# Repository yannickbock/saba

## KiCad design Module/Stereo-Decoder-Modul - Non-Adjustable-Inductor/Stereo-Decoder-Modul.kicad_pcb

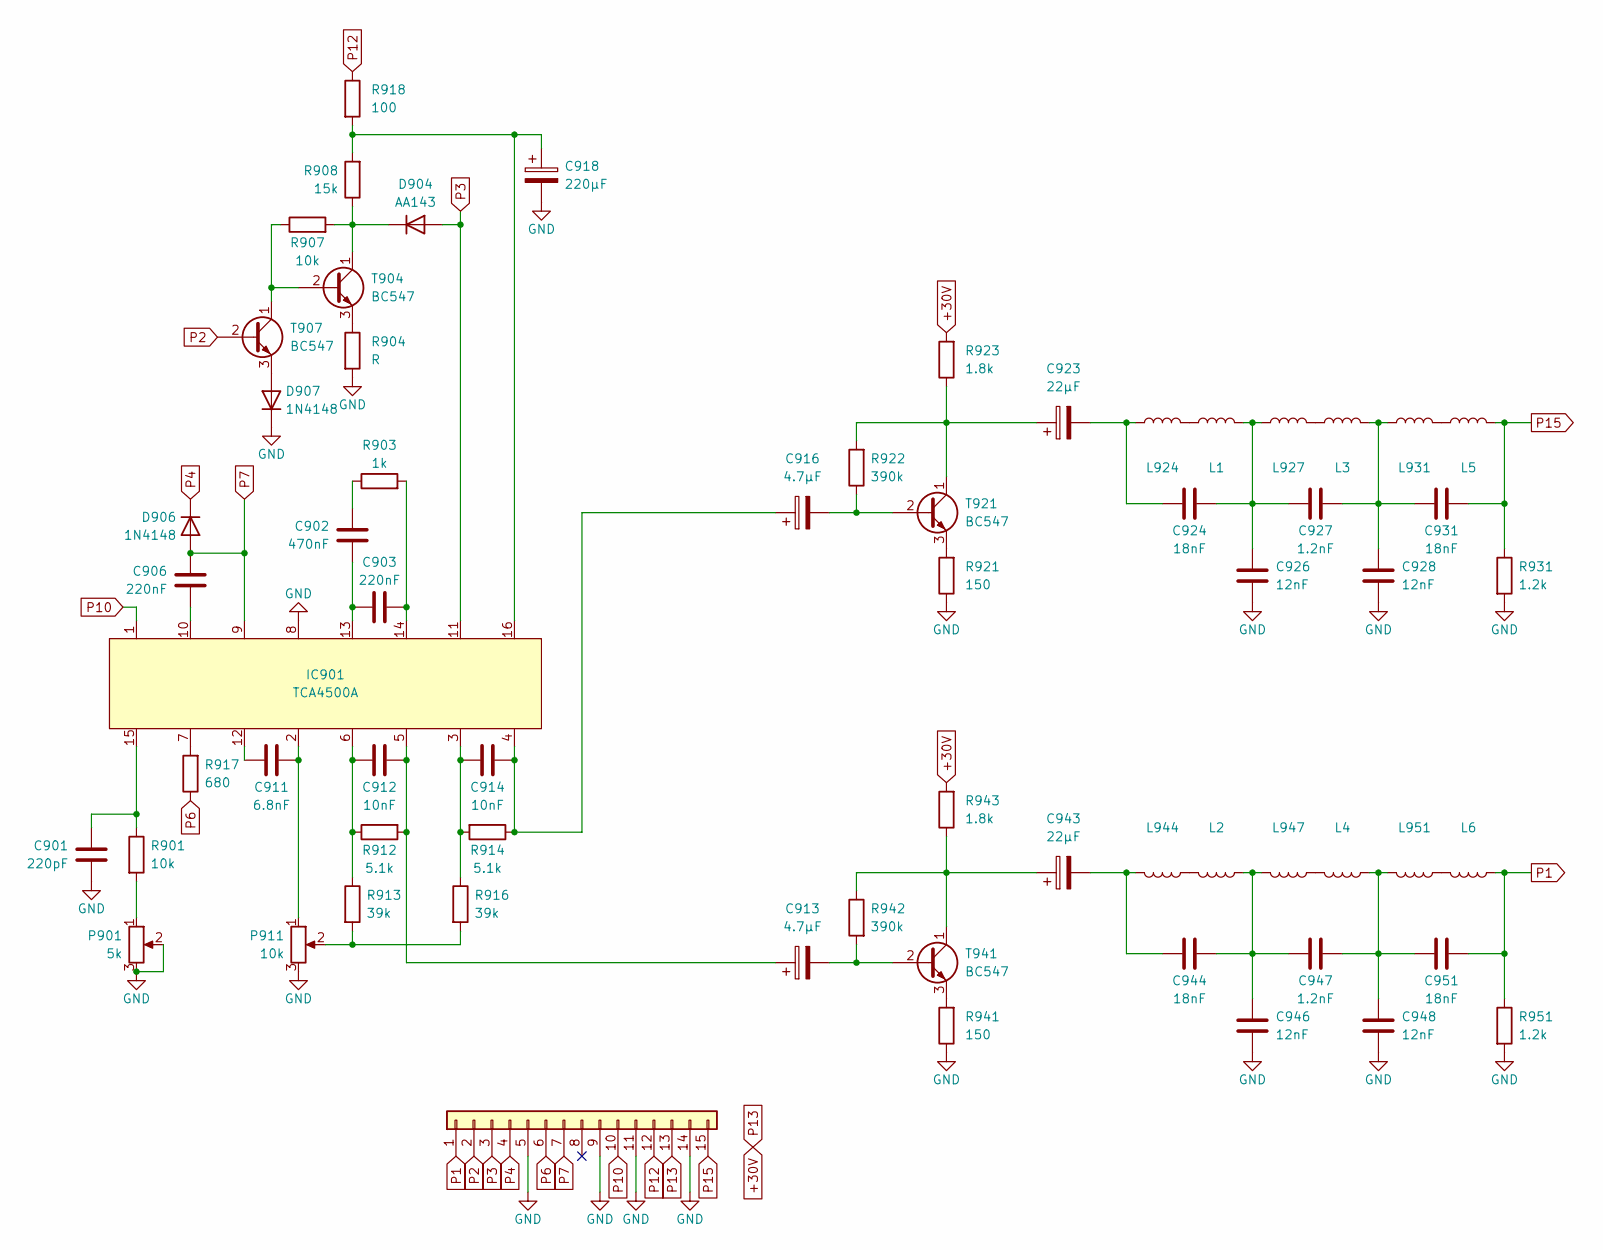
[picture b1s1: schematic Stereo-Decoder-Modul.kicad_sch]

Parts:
C901: 220pF; C_Rect_L7.2mm_W3.0mm_P5.00mm_FKS2_FKP2_MKS2_MKP2
C902: 470nF; C_Rect_L7.2mm_W3.0mm_P5.00mm_FKS2_FKP2_MKS2_MKP2
C903, C906: 220nF; C_Rect_L7.2mm_W3.0mm_P5.00mm_FKS2_FKP2_MKS2_MKP2
C911: 6.8nF; C_Rect_L7.2mm_W3.0mm_P5.00mm_FKS2_FKP2_MKS2_MKP2
C912, C914: 10nF; C_Rect_L10.0mm_W3.0mm_P7.50mm_MKS4
C913, C916: 4.7µF; C_Rect_L7.2mm_W7.2mm_P5.00mm_FKS2_FKP2_MKS2_MKP2
C918: 220µF; CP_Radial_D8.0mm_P3.50mm
C923, C943: 22µF; CP_Radial_D5.0mm_P2.00mm
C924, C931, C944, C951: 18nF; C_Rect_L10.0mm_W3.0mm_P7.50mm_MKS4
C926, C928, C946, C948: 12nF; C_Rect_L10.0mm_W3.0mm_P7.50mm_MKS4
C927, C947: 1.2nF; C_Rect_L10.0mm_W3.0mm_P7.50mm_MKS4
D904: AA143; D_DO-35_SOD27_P5.08mm_Vertical_AnodeUp
D906, D907: 1N4148; D_DO-35_SOD27_P5.08mm_Vertical_AnodeUp
IC901: TCA4500A; DIP-16_W7.62mm_LongPads
J1: Conn_01x15; Connector_01x15_5mm
L1, L2, L3, L4, L5, L6, L924, L927, L931, L944, L947, L951: 3.3mH-4.7mH; L_Axial_L11.0mm_D4.5mm_P5.08mm_Vertical_Fastron_MECC
P901: 5k; Potentiometer_Piher_PT-10-H01_Horizontal
P911: 10k; Potentiometer_Piher_PT-10-H01_Horizontal
R901, R907: 10k; R_Axial_DIN0207_L6.3mm_D2.5mm_P5.08mm_Vertical
R903: 1k; R_Axial_DIN0207_L6.3mm_D2.5mm_P5.08mm_Vertical
R904: R; R_Axial_DIN0207_L6.3mm_D2.5mm_P5.08mm_Vertical
R908: 15k; R_Axial_DIN0207_L6.3mm_D2.5mm_P5.08mm_Vertical
R912, R914: 5.1k; R_Axial_DIN0207_L6.3mm_D2.5mm_P2.54mm_Vertical
R913, R916: 39k; R_Axial_DIN0207_L6.3mm_D2.5mm_P5.08mm_Vertical
R917: 680; R_Axial_DIN0207_L6.3mm_D2.5mm_P5.08mm_Vertical
R918: 100; R_Axial_DIN0207_L6.3mm_D2.5mm_P5.08mm_Vertical
R921, R941: 150; R_Axial_DIN0207_L6.3mm_D2.5mm_P5.08mm_Vertical
R922, R942: 390k; R_Axial_DIN0207_L6.3mm_D2.5mm_P5.08mm_Vertical
R923, R943: 1.8k; R_Axial_DIN0207_L6.3mm_D2.5mm_P5.08mm_Vertical
R931, R951: 1.2k; R_Axial_DIN0207_L6.3mm_D2.5mm_P5.08mm_Vertical
T904, T907, T921, T941: BC547; TO-92_Wide

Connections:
+30V: J1.13, R923.2, R943.2
GND: C901.1, C918.2, C926.2, C928.2, C946.2, C948.2, D907.1 (K), IC901.8, J1.5, J1.9, J1.11, J1.14, P901.2, P901.3, P911.3, R904.2, R921.1, R931.2, R941.1, R951.2
unnamed: C901.2, IC901.15, R901.1
unnamed: C902.1, R903.1
unnamed: C902.2, C903.1, IC901.13
unnamed: C903.2, IC901.14, R903.2
unnamed: C906.2, IC901.10
unnamed: C911.1, IC901.12
unnamed: C911.2, IC901.2, P911.1
unnamed: C912.1, C913.1, IC901.5, R912.2
unnamed: C912.2, IC901.6, R912.1, R913.1
unnamed: C913.2, R942.2, T941.2 (B)
unnamed: C914.1, IC901.3, R914.2, R916.1
unnamed: C914.2, C916.1, IC901.4, R914.1
unnamed: C916.2, R922.1, T921.2 (B)
unnamed: C918.1, IC901.16, R908.2, R918.2
unnamed: C923.1, R922.2, R923.1, T921.1 (C)
unnamed: C923.2, C924.1, L924.2
unnamed: C924.2, C926.1, C927.1, L1.1, L927.2
unnamed: C927.2, C928.1, C931.1, L3.1, L931.2
unnamed: C943.1, R942.1, R943.1, T941.1 (C)
unnamed: C943.2, C944.1, L944.1
unnamed: C944.2, C946.1, C947.1, L2.2, L947.1
unnamed: C947.2, C948.1, C951.1, L4.2, L951.1
unnamed: D904.1 (K), R907.2, R908.1, T904.1 (C)
unnamed: D907.2 (A), T907.3 (E)
unnamed: IC901.7, R917.2
unnamed: L1.2, L924.1
unnamed: L3.2, L927.1
unnamed: L5.2, L931.1
unnamed: L2.1, L944.2
unnamed: L4.1, L947.2
unnamed: L6.1, L951.2
unnamed: P901.1, R901.2
unnamed: P911.2, R913.2, R916.2
unnamed: R904.1, T904.3 (E)
unnamed: R907.1, T904.2 (B), T907.1 (C)
unnamed: R921.2, T921.3 (E)
unnamed: R941.2, T941.3 (E)
P1: C951.2, J1.1, L6.2, R951.1
P2: J1.2, T907.2 (B)
P3: D904.2 (A), IC901.11, J1.3
P4: D906.1 (K), J1.4
P6: J1.6, R917.1
P7: C906.1, D906.2 (A), IC901.9, J1.7
P10: IC901.1, J1.10
P12: J1.12, R918.1
P15: C931.2, J1.15, L5.1, R931.1

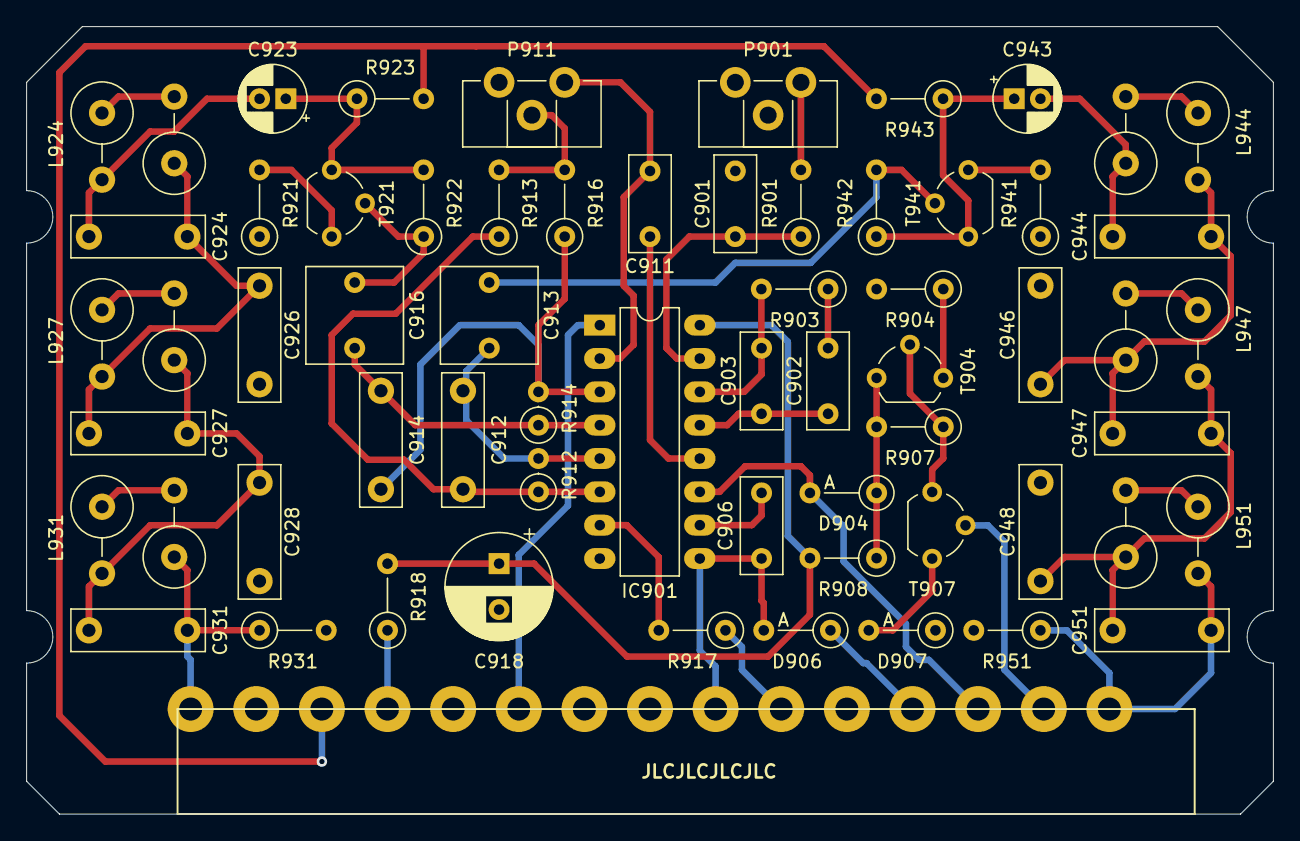
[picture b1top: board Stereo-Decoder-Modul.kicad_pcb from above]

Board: 2 copper layers, 95.0 x 60.0 mm, 64 parts (0 on the bottom side), 48 nets.

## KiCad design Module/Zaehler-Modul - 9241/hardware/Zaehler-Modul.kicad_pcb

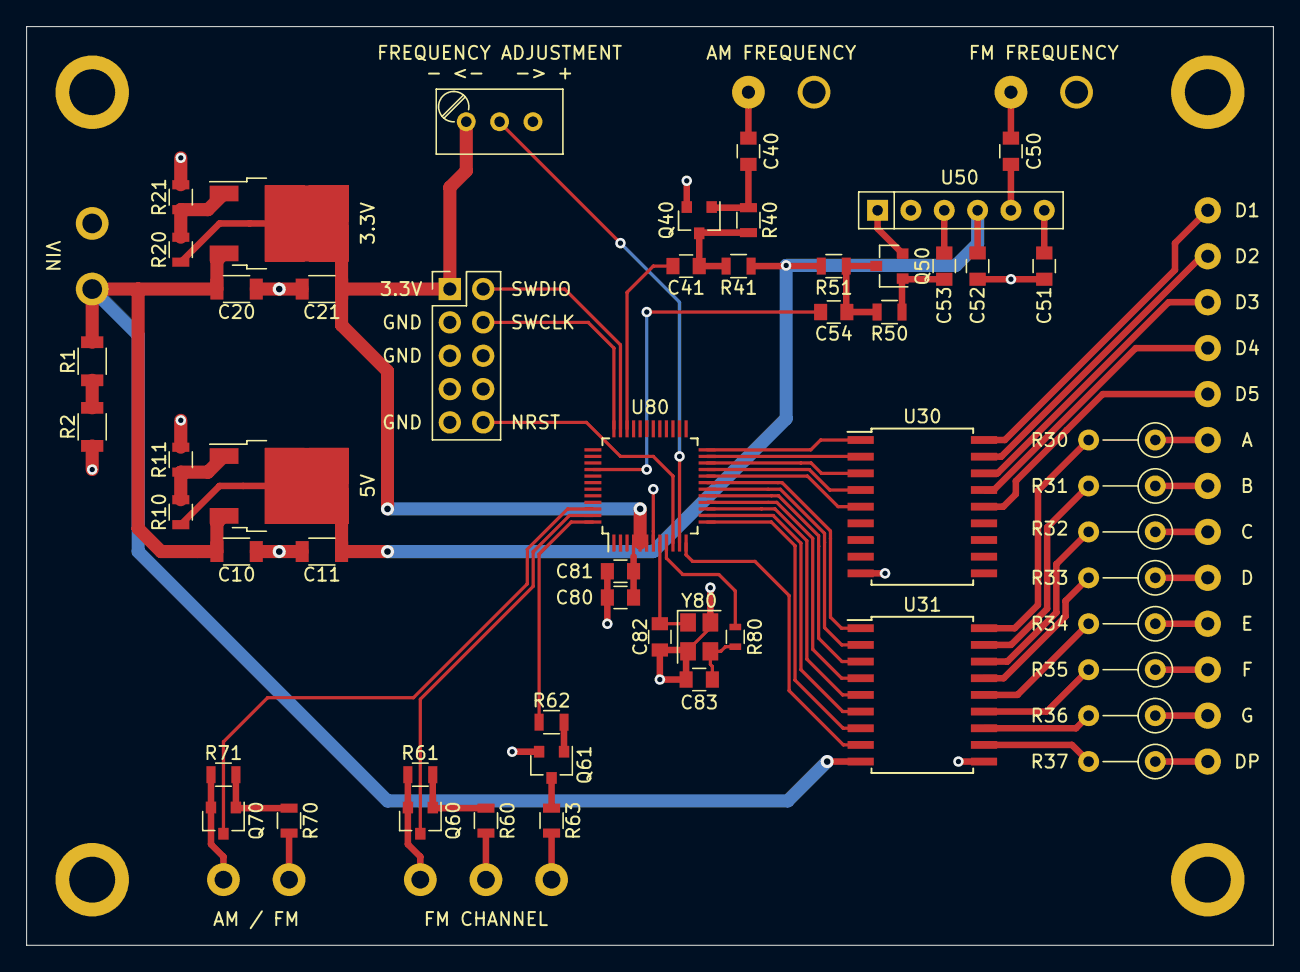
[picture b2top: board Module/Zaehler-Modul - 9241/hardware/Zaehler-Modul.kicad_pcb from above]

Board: 2 copper layers, 95.0 x 70.0 mm, 70 parts (0 on the bottom side), 69 nets.

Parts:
C10, C11, C20, C21: 10µF; C_1206
C40, C41, C50, C51, C53, C54: 1nF; C_0805
C52: 22nF; C_0805
C80: 2.2µF; C_0805
C81: 100nF; C_0805
C82, C83: 12pF; C_0805
H1, H2, H3, H4: MountingHole_Pad; MountingHole_3.2mm_M3_DIN965_Pad
J2, J3, J4, J6, J7, J8, J9, J10, J11, J12, J13: Conn_01x01; SolderWirePad_single_1-2mmDrill
J5: SWD; Pin_Header_Straight_2x05_Pitch2.54mm
J14: Conn_01x13; Conn_01x13_3.5mm
Q40, Q50, Q60, Q61, Q70: BC847; SOT-23
R1, R2: 300; R_1206
R10, R20: 240; R_0805
R11: 680; R_0805
R21: 390; R_0805
R30, R31, R32, R33, R34, R35, R36, R37: 470; R_Axial_DIN0207_L6.3mm_D2.5mm_P5.08mm_Vertical
R40, R50, R61, R71: 100k; R_0805
R41, R51, R63: 1k; R_0805
R60, R70: 33k; R_0805
R62: 3.3k; R_0805
R80: 47; R_0603
RV80: 100k; Potentiometer_Trimmer_Bourns_3296W
U10, U20: LM317; TO-252-2
U30: ULN2803A; SOIC-18W_7.5x11.6mm_Pitch1.27mm
U31: UDN2981; SOIC-18W_7.5x11.6mm_Pitch1.27mm
U50: U813BS; R_Array_SIP6
U80: STM32G030C8T6; LQFP-48_7x7mm_Pitch0.5mm
Y80: 16MHz; Crystal_SMD_3225-4pin_3.2x2.5mm

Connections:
+3V3: C21.1, C80.1, C81.1, J5.1, R20.1, RV80.1, U20.2, U80.4, U80.5, U80.6
+5V: C11.1, C52.1, R10.1, R41.1, R51.1, U10.2, U50.4
+12V: C10.1, C20.1, J10.1, R1.1, U10.3, U20.3, U31.9
A: J14.6, R30.1
AM_FREQUENCY: C41.1, U80.34
B: J14.7, R31.1
C: J14.8, R32.1
D: J14.9, R33.1
D1: J14.1, U30.18
D2: J14.2, U30.17
D3: J14.3, U30.16
D4: J14.4, U30.15
D5: J14.5, U30.14
DP: J14.13, R37.1
DP_A: U31.1, U80.19
DP_B: U31.2, U80.18
DP_C: U31.3, U80.17
DP_D: U31.4, U80.16
DP_D1: U30.1, U80.24
DP_D2: U30.2, U80.23
DP_D3: U30.3, U80.22
DP_D4: U30.4, U80.21
DP_D5: U30.5, U80.20
DP_DP: U31.8, U80.12
DP_E: U31.5, U80.15
DP_F: U31.6, U80.14
DP_G: U31.7, U80.13
E: J14.10, R34.1
F: J14.11, R35.1
FM_FREQUENCY: C54.1, U80.40
FREQUENCY_CALIBRATION: RV80.2, U80.11
G: J14.12, R36.1
GND: C10.2, C11.2, C20.2, C21.2, C51.2, C52.2, C80.2, C81.2, C82.2, C83.2, H1.1, H2.1, H3.1, H4.1, J5.3, J5.5, J5.9, J6.1, J9.1, J11.1, J12.1, J13.1, Q40.2, Q50.2, Q60.2, Q61.2, Q70.2, R2.2, R11.2, R21.2, R61.2, R71.2, RV80.3, U30.9, U31.10, U50.1, U80.7, Y80.2, Y80.4
HSE_IN: C82.1, U80.8, Y80.1
HSE_OUT: R80.1, U80.9
NRST: J5.10, U80.10
unnamed: C40.1, Q40.1, R40.2
unnamed: C40.2, J8.1
unnamed: C41.2, Q40.3, R40.1, R41.2
unnamed: C50.1, U50.5
unnamed: C50.2, J7.1
unnamed: C51.1, U50.6
unnamed: C53.1, Q50.1, R50.2
unnamed: C53.2, U50.3
unnamed: C54.2, Q50.3, R50.1, R51.2
unnamed: C83.1, R80.2, Y80.3
unnamed: J2.1, R63.1
unnamed: J3.1, R60.2
unnamed: J4.1, R70.2
unnamed: Q60.1, R60.1, R61.1
unnamed: Q61.1, R62.1
unnamed: Q61.3, R63.2
unnamed: Q70.1, R70.1, R71.1
unnamed: R1.2, R2.1
unnamed: R10.2, R11.1, U10.1
unnamed: R20.2, R21.1, U20.1
unnamed: R30.2, U31.18
unnamed: R31.2, U31.17
unnamed: R32.2, U31.16
unnamed: R33.2, U31.15
unnamed: R34.2, U31.14
unnamed: R35.2, U31.13
unnamed: R36.2, U31.12
unnamed: R37.2, U31.11
SWCLK: J5.4, U80.36
SWDIO: J5.2, U80.35
am_fm: Q70.3, U80.46
fm_channel: Q60.3, U80.47
led_fm_channel: R62.2, U80.48

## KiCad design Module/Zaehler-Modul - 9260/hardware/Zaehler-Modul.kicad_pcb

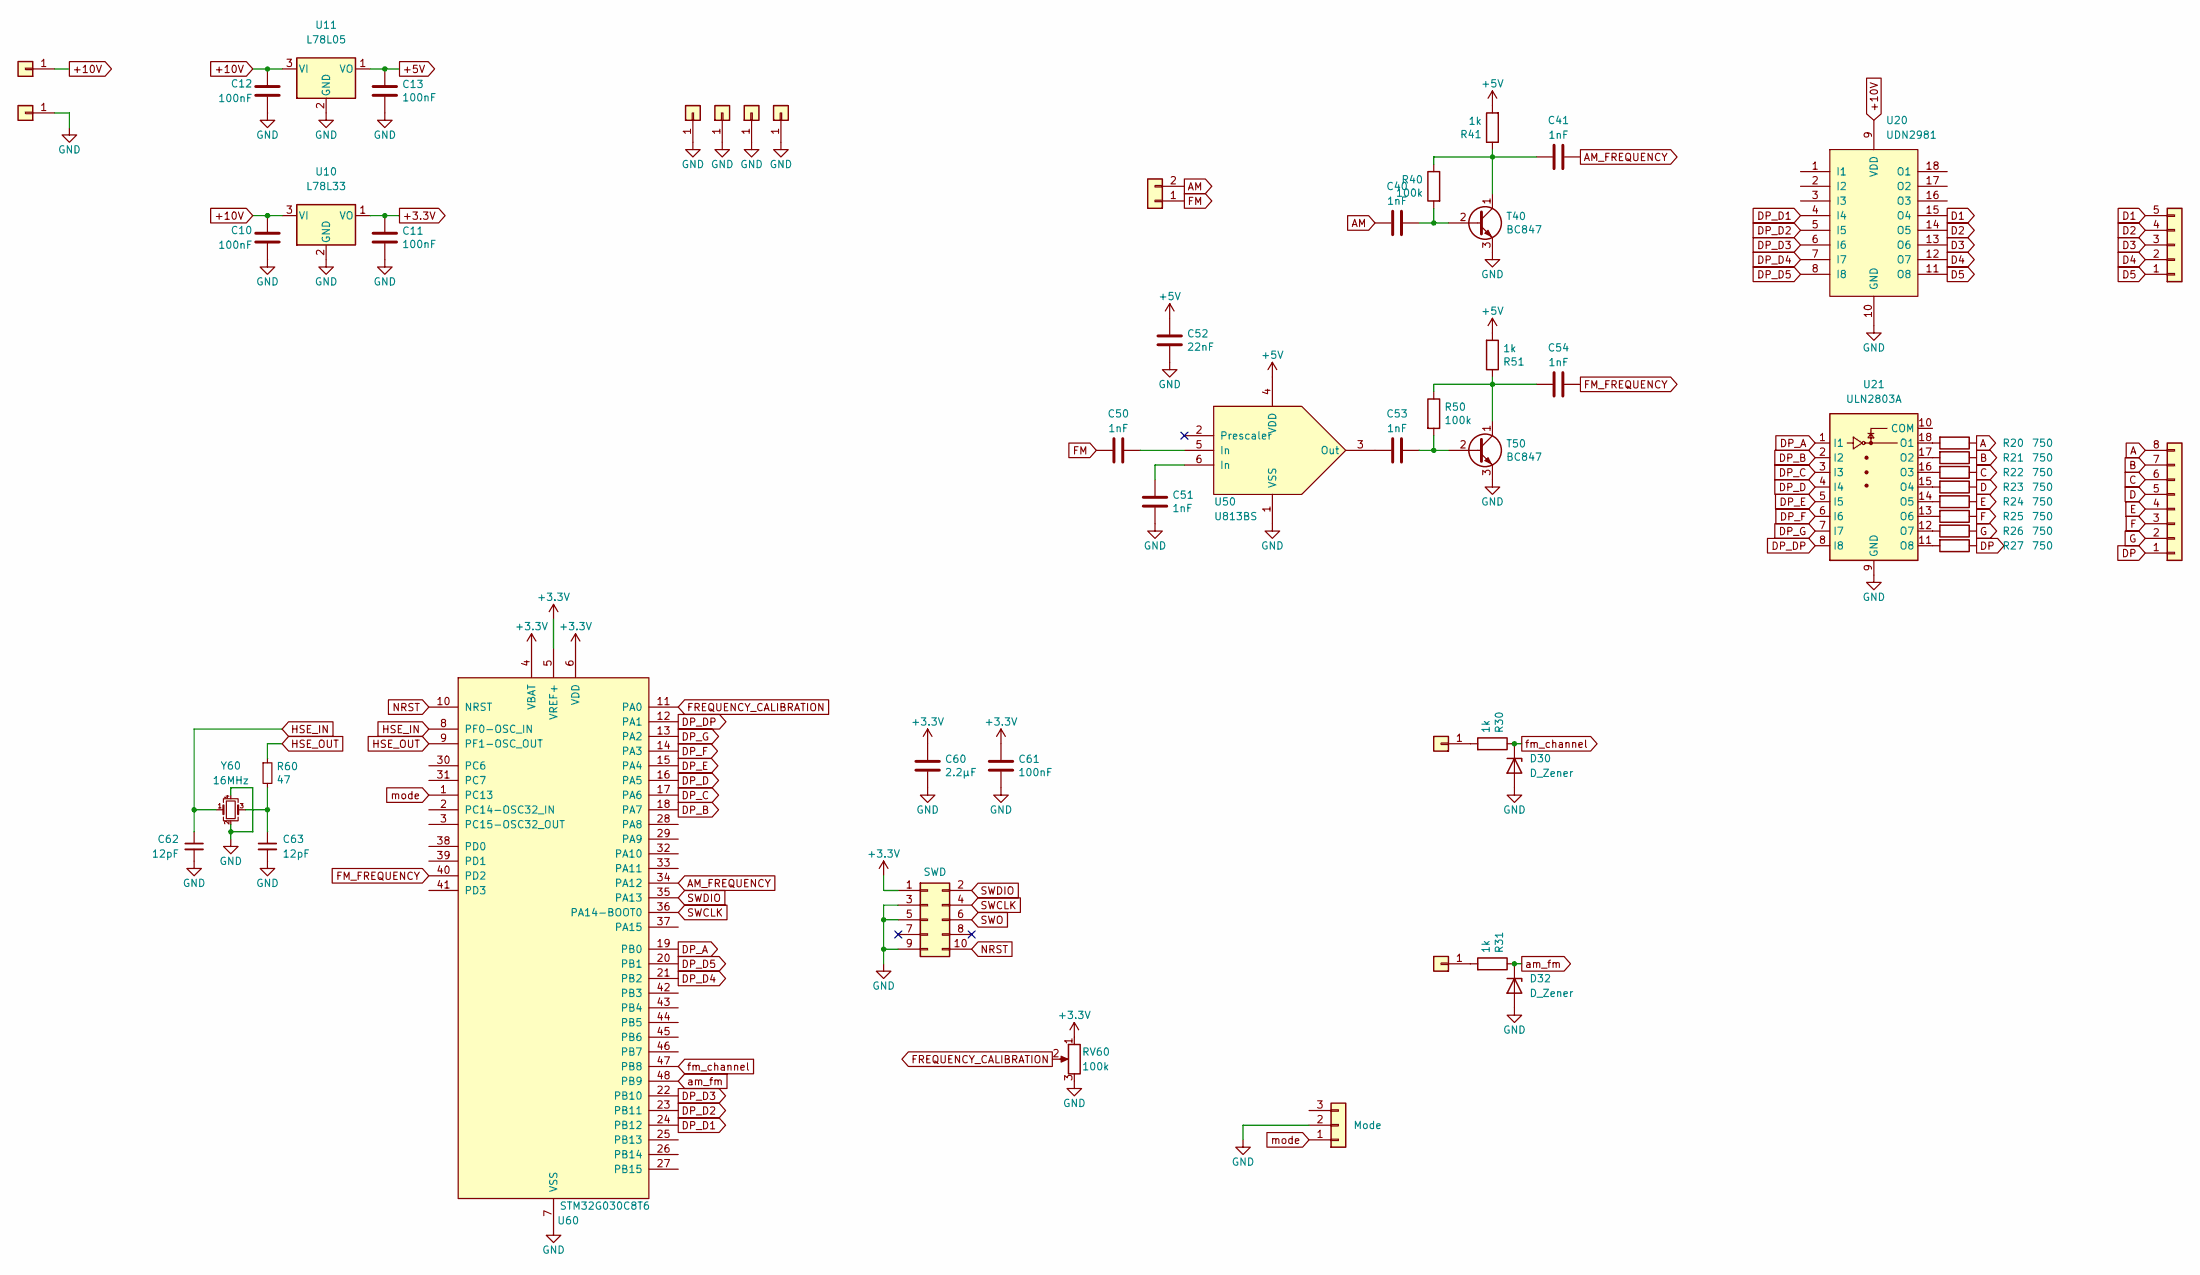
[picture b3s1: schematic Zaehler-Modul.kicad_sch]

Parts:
C10, C11, C12, C13: 100nF; C_Rect_L7.0mm_W2.5mm_P5.00mm; LCSC C13585
C40, C41, C50, C51, C53, C54: 1nF; C_Disc_D6.0mm_W2.5mm_P5.00mm; LCSC C46653
C52: 22nF; C_Disc_D6.0mm_W2.5mm_P5.00mm; LCSC C1729
C60: 2.2µF; C_0805_2012Metric; LCSC C49217
C61: 100nF; C_0805_2012Metric; LCSC C49678
C62, C63: 12pF; C_0805_2012Metric; LCSC C1804
D30, D32: D_Zener; D_DO-35_SOD27_P5.08mm_Vertical_AnodeUp
J1: Conn_01x02
J2, J3, J4, J6: Conn_01x01; TestPoint_Plated_Hole_D2.0mm
J5: SWD; PinHeader_2x05_P2.54mm_Vertical
J7: Conn_01x05; PinSocket_1x05_P2.54mm_Horizontal
J8: Conn_01x08; PinSocket_1x08_P2.54mm_Horizontal
J9, J10, J11, J13: Conn_01x01; Solderpad_08x05
J12: Mode; PinHeader_1x03_P2.54mm_Vertical
R20, R21, R22, R23, R24, R25, R26, R27: 750; R_1206_3216Metric; LCSC C17985
R30, R31: 1k; R_Axial_DIN0207_L6.3mm_D2.5mm_P5.08mm_Vertical; LCSC C149504
R40, R50: 100k; R_Axial_DIN0207_L6.3mm_D2.5mm_P5.08mm_Vertical; LCSC C149504
R41, R51: 1k; R_Axial_DIN0207_L6.3mm_D2.5mm_P5.08mm_Vertical; LCSC C17513
R60: 47; R_0603_1608Metric; LCSC C23182
RV60: 100k; Potentiometer_Piher_PT-10-H01_Horizontal
T40, T50: BC847; TO-92_Wide; LCSC C2150
U10: L78L33; TO-92_Wide
U11: L78L05; TO-92_Wide
U20: UDN2981; DIP-18_W7.62mm_LongPads
U21: ULN2803A; DIP-18_W7.62mm_LongPads
U50: U813BS; R_Array_SIP6
U60: STM32G030C8T6; LQFP-48_7x7mm_P0.5mm; LCSC C529329
Y60: 16MHz; Crystal_SMD_3225-4Pin_3.2x2.5mm; LCSC C13738

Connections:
+3.3V: C11.1, C60.1, C61.1, J5.1, RV60.1, U10.1 (VO), U60.4 (VBAT), U60.5 (VREF+), U60.6 (VDD)
+5V: C13.1, C52.1, R41.2, R51.2, U11.1 (VO), U50.4 (VDD)
+10V: C10.1, C12.1, J4.1, U10.3 (VI), U11.3 (VI), U20.9 (VDD)
A: J8.8, R20.1
AM: C40.2, J1.2
AM_FREQUENCY: C41.1, U60.34 (PA12)
B: J8.7, R21.1
C: J8.6, R22.1
D: J8.5, R23.1
D1: J7.5, U20.15 (O4)
D2: J7.4, U20.14 (O5)
D3: J7.3, U20.13 (O6)
D4: J7.2, U20.12 (O7)
D5: J7.1, U20.11 (O8)
DP: J8.1, R27.1
DP_A: U21.1 (I1), U60.19 (PB0)
DP_B: U21.2 (I2), U60.18 (PA7)
DP_C: U21.3 (I3), U60.17 (PA6)
DP_D: U21.4 (I4), U60.16 (PA5)
DP_D1: U20.4 (I4), U60.24 (PB12)
DP_D2: U20.5 (I5), U60.23 (PB11)
DP_D3: U20.6 (I6), U60.22 (PB10)
DP_D4: U20.7 (I7), U60.21 (PB2)
DP_D5: U20.8 (I8), U60.20 (PB1)
DP_DP: U21.8 (I8), U60.12 (PA1)
DP_E: U21.5 (I5), U60.15 (PA4)
DP_F: U21.6 (I6), U60.14 (PA3)
DP_G: U21.7 (I7), U60.13 (PA2)
E: J8.4, R24.1
F: J8.3, R25.1
FM: C50.2, J1.1
FM_FREQUENCY: C54.1, U60.40 (PD2)
FREQUENCY_CALIBRATION: RV60.2, U60.11 (PA0)
G: J8.2, R26.1
GND: C10.2, C11.2, C12.2, C13.2, C51.2, C52.2, C60.2, C61.2, C62.2, C63.2, D30.2 (A), D32.2 (A), J5.3, J5.5, J5.9, J6.1, J9.1, J10.1, J11.1, J12.2, J13.1, RV60.3, T40.3 (E), T50.3 (E), U10.2 (GND), U11.2 (GND), U20.10 (GND), U21.9 (GND), U50.1 (VSS), U60.7 (VSS), Y60.2, Y60.4
HSE_IN: C62.1, U60.8 (PF0-OSC_IN), Y60.1
HSE_OUT: R60.1, U60.9 (PF1-OSC_OUT)
NRST: J5.10, U60.10 (NRST)
unnamed: C40.1, R40.2, T40.2 (B)
unnamed: C41.2, R40.1, R41.1, T40.1 (C)
unnamed: C50.1, U50.5 (In)
unnamed: C51.1, U50.6 (In)
unnamed: C53.1, R50.2, T50.2 (B)
unnamed: C53.2, U50.3 (Out)
unnamed: C54.2, R50.1, R51.1, T50.1 (C)
unnamed: C63.1, R60.2, Y60.3
unnamed: J2.1, R30.2
unnamed: J3.1, R31.2
unnamed: R20.2, U21.18 (O1)
unnamed: R21.2, U21.17 (O2)
unnamed: R22.2, U21.16 (O3)
unnamed: R23.2, U21.15 (O4)
unnamed: R24.2, U21.14 (O5)
unnamed: R25.2, U21.13 (O6)
unnamed: R26.2, U21.12 (O7)
unnamed: R27.2, U21.11 (O8)
SWCLK: J5.4, U60.36 (PA14-BOOT0)
SWDIO: J5.2, U60.35 (PA13)
SWO: J5.6
am_fm: D32.1 (K), R31.1, U60.48 (PB9)
fm_channel: D30.1 (K), R30.1, U60.47 (PB8)
mode: J12.1, U60.1 (PC13)

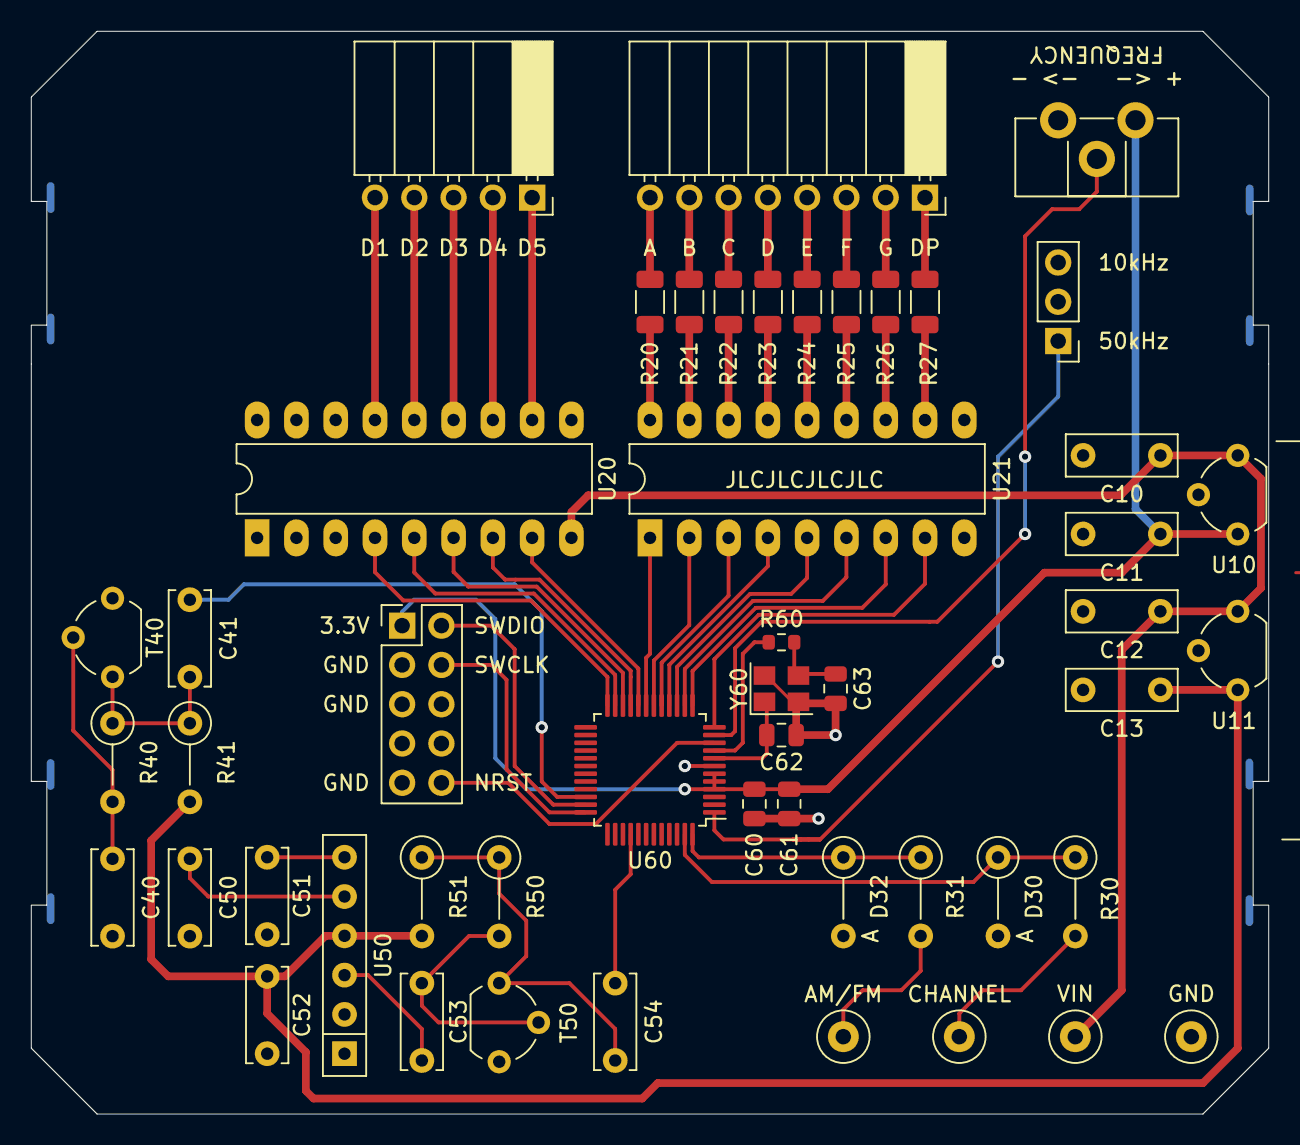
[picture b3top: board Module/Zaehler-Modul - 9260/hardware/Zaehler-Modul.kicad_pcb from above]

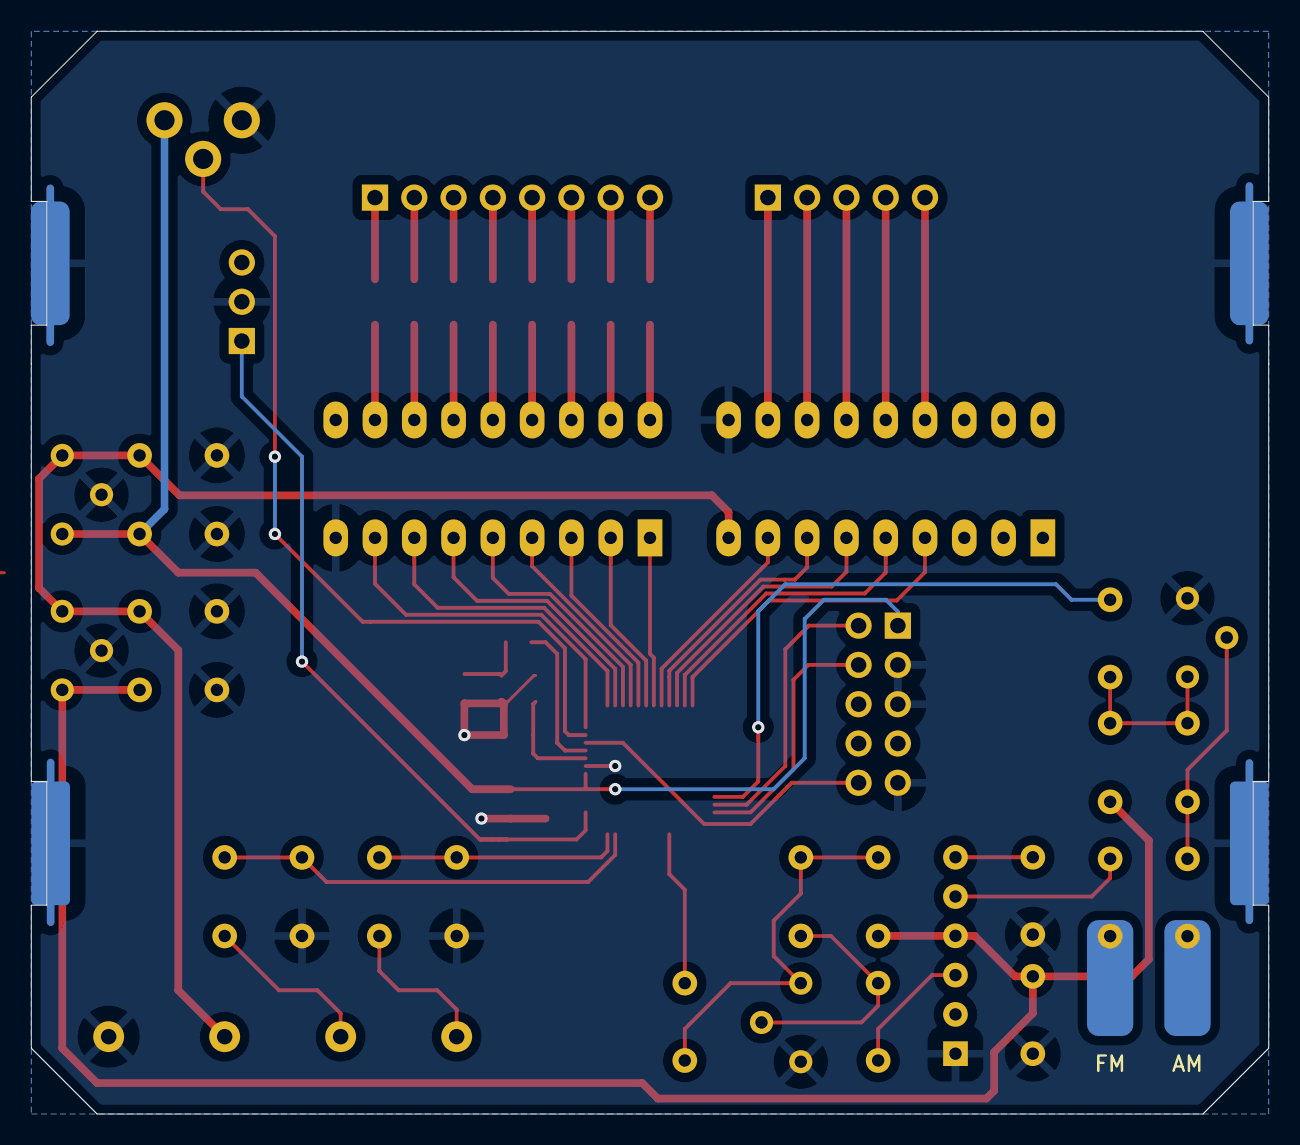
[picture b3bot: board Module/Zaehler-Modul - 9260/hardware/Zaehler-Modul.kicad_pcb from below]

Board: 2 copper layers, 80.0 x 70.0 mm, 55 parts (3 on the bottom side), 61 nets.

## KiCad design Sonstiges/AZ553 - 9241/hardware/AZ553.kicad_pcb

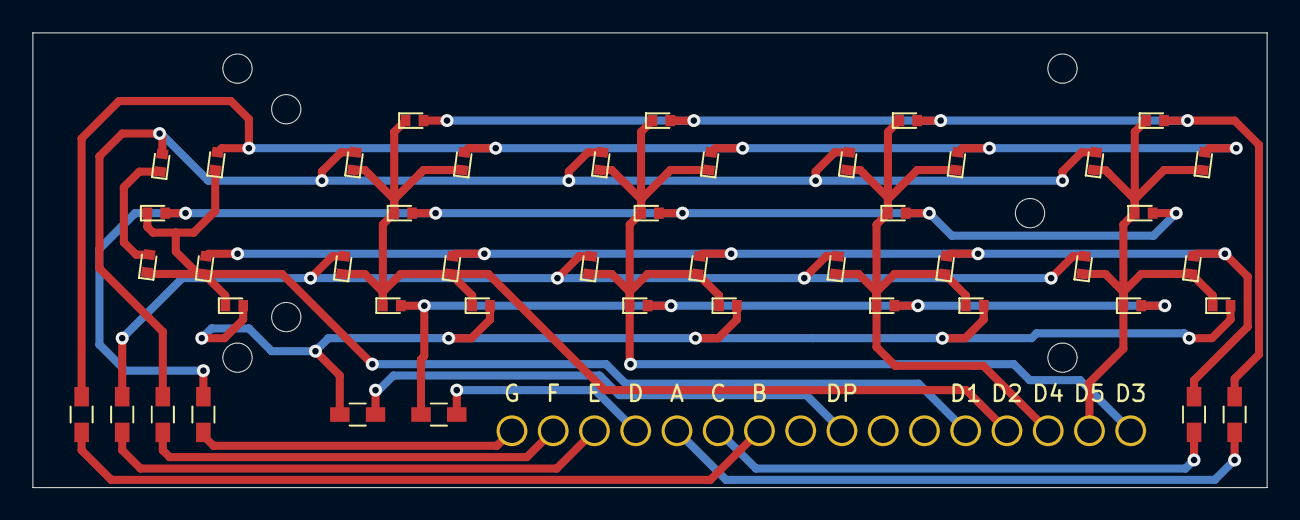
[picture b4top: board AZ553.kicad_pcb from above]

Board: 2 copper layers, 76.0 x 28.0 mm, 47 parts (1 on the bottom side), 22 nets.

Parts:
D1, D2, D3, D4, D5, D6, D7, D8, D9, D10, D11, D12, D13, D14, D15, D16, D17, D18, D19, D20, D21, D22, D23, D24, D25, D26, D27, D28, D29, D30, D31, D32, D33, D34, D35, D36, D37, D38: LED; LED_0402
J1: Conn_01x16; Pin_Header_Straight_1x16_Pitch2.54mm
R1, R2, R3, R4, R5, R6, R7, R8: 2.2k; R_0603_HandSoldering

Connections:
A: D1.2, D9.2, D19.2, D20.2, R5.1
B: D5.2, D11.2, D17.2, D18.2, D27.2, R7.1
C: D7.2, D14.2, D23.2, D30.2, D34.2, R6.1
D: D8.2, D15.2, D25.2, D32.2, R4.1
D1: D17.1, D34.1, D36.1, D37.1, D38.1, J1.12
D2: D20.1, D27.1, D28.1, D29.1, D30.1, D31.1, D32.1, D33.1, J1.13
D3: D18.1, D19.1, D21.1, D22.1, D23.1, D24.1, D25.1, D26.1, J1.16
D4: D9.1, D10.1, D11.1, D12.1, D13.1, D14.1, D15.1, D16.1, J1.14
D5: D1.1, D2.1, D3.1, D4.1, D5.1, D6.1, D7.1, D8.1, J1.15
DP: D6.2, D16.2, D26.2, D33.2, D37.2, R8.1
E: D4.2, D13.2, D24.2, D31.2, R3.1
F: D2.2, D10.2, D21.2, D29.2, D35.2, R2.1
G: D3.2, D12.2, D22.2, D28.2, D38.2, R1.1
unnamed: D35.1, D36.2
unnamed: J1.1, R1.2
unnamed: J1.2, R2.2
unnamed: J1.3, R3.2
unnamed: J1.4, R4.2
unnamed: J1.5, R5.2
unnamed: J1.6, R6.2
unnamed: J1.7, R7.2
unnamed: J1.9, R8.2

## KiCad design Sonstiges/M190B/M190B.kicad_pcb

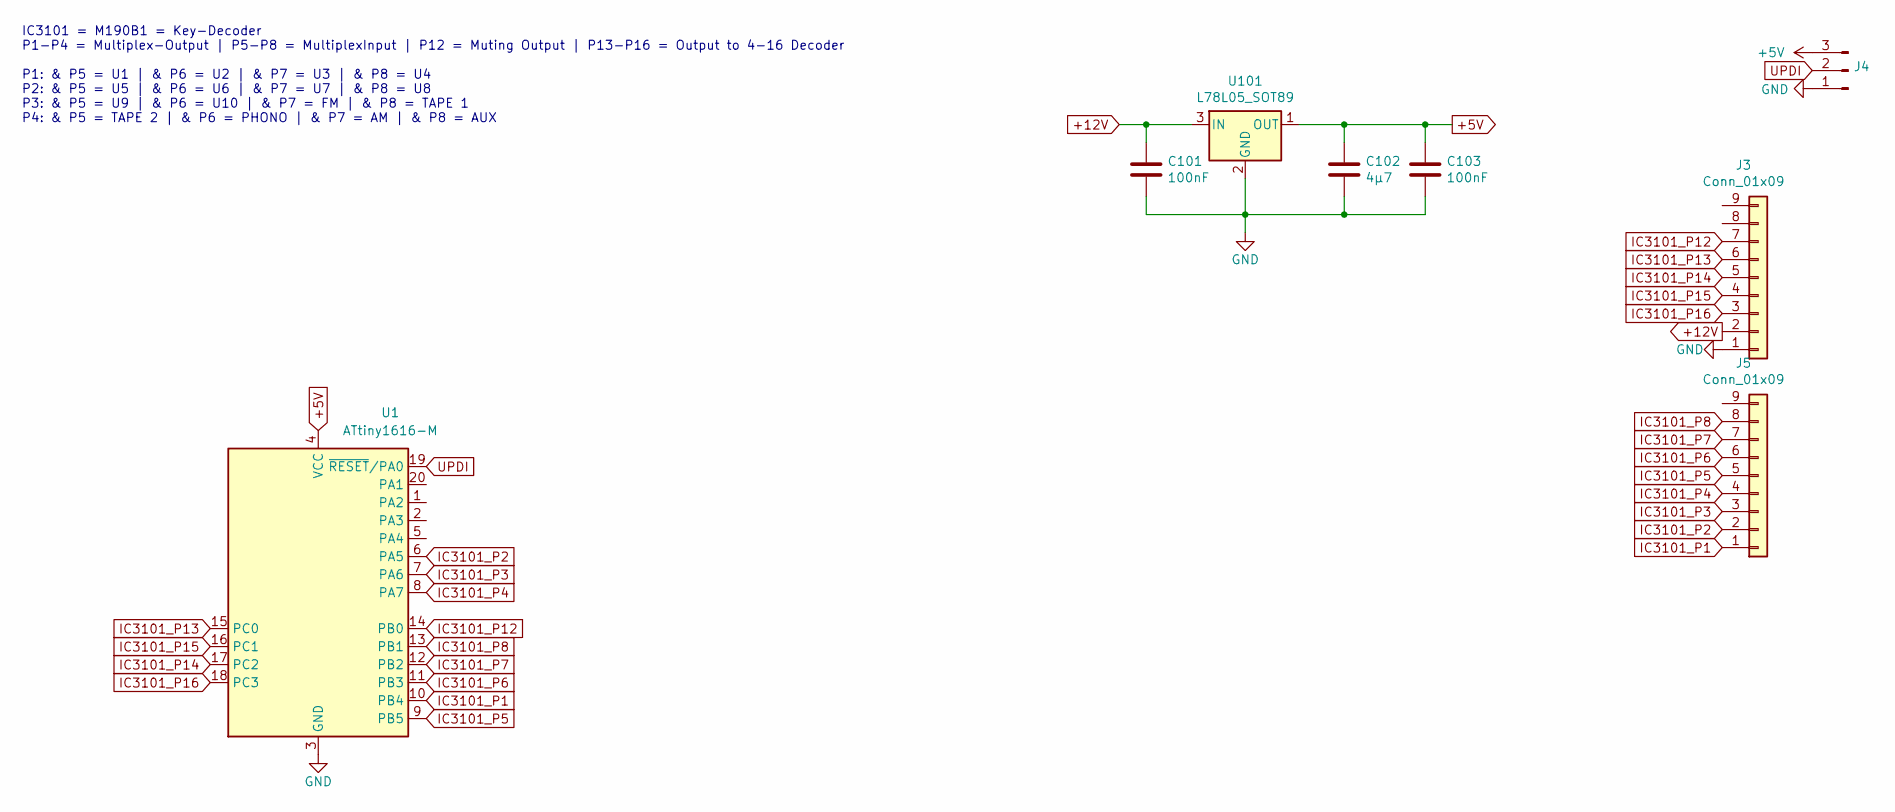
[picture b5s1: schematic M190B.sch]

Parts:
C101, C103: 100nF; C_0402; LCSC C1525
C102: 4µ7; C_0402; LCSC C23733
J3, J5: Conn_01x09; Pin_Header_Straight_1x09_Pitch2.54mm
J4: Conn_01x03_Male; Pin_Header_Straight_1x03_Pitch2.54mm
U1: ATtiny1616-M; UQFN-20-1EP_3x3mm_Pitch0.4mm; LCSC C507118
U101: L78L05_SOT89; SOT-89-3; LCSC C71136

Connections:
+5V: C102.1, C103.1, J4.3, U1.4 (VCC), U101.1 (OUT)
+12V: C101.1, J3.2, U101.3 (IN)
GND: C101.2, C102.2, C103.2, J3.1, J4.1, U1.3 (GND), U1.21 (GND), U101.2 (GND)
IC3101_P1: J5.1, U1.10 (PB4)
IC3101_P2: J5.2, U1.6 (PA5)
IC3101_P3: J5.3, U1.7 (PA6)
IC3101_P4: J5.4, U1.8 (PA7)
IC3101_P5: J5.5, U1.9 (PB5)
IC3101_P6: J5.6, U1.11 (PB3)
IC3101_P7: J5.7, U1.12 (PB2)
IC3101_P8: J5.8, U1.13 (PB1)
IC3101_P12: J3.7, U1.14 (PB0)
IC3101_P13: J3.6, U1.15 (PC0)
IC3101_P14: J3.5, U1.17 (PC2)
IC3101_P15: J3.4, U1.16 (PC1)
IC3101_P16: J3.3, U1.18 (PC3)
UPDI: J4.2, U1.19 (~RESET~/PA0)

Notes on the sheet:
IC3101 = M190B1 = Key-Decoder P1-P4 = Multiplex-Output | P5-P8 = MultiplexInput | P12 = Muting Output | P13-P16 = Output to 4-16 Decoder P1: & P5 = U1 | & P6 = U2 | & P7 = U3 | & P8 = U4 P2: & P5 = U5 | & P6 = U6 | & P7 = U7 | & P8 = U8 P3: & P5 = U9 | & P6 = U10 | & P7 = FM | & P8 = TAPE 1 P4: & P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

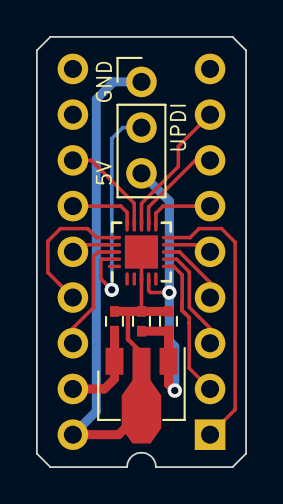
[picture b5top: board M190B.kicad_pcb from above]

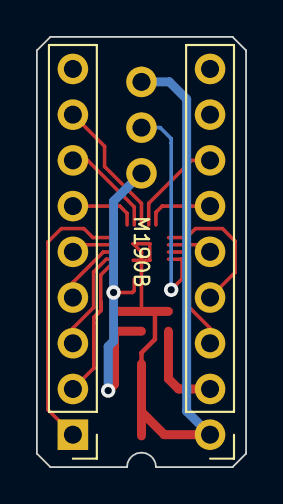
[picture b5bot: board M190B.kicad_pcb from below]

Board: 2 copper layers, 11.6 x 23.9 mm, 8 parts (2 on the bottom side), 17 nets.
